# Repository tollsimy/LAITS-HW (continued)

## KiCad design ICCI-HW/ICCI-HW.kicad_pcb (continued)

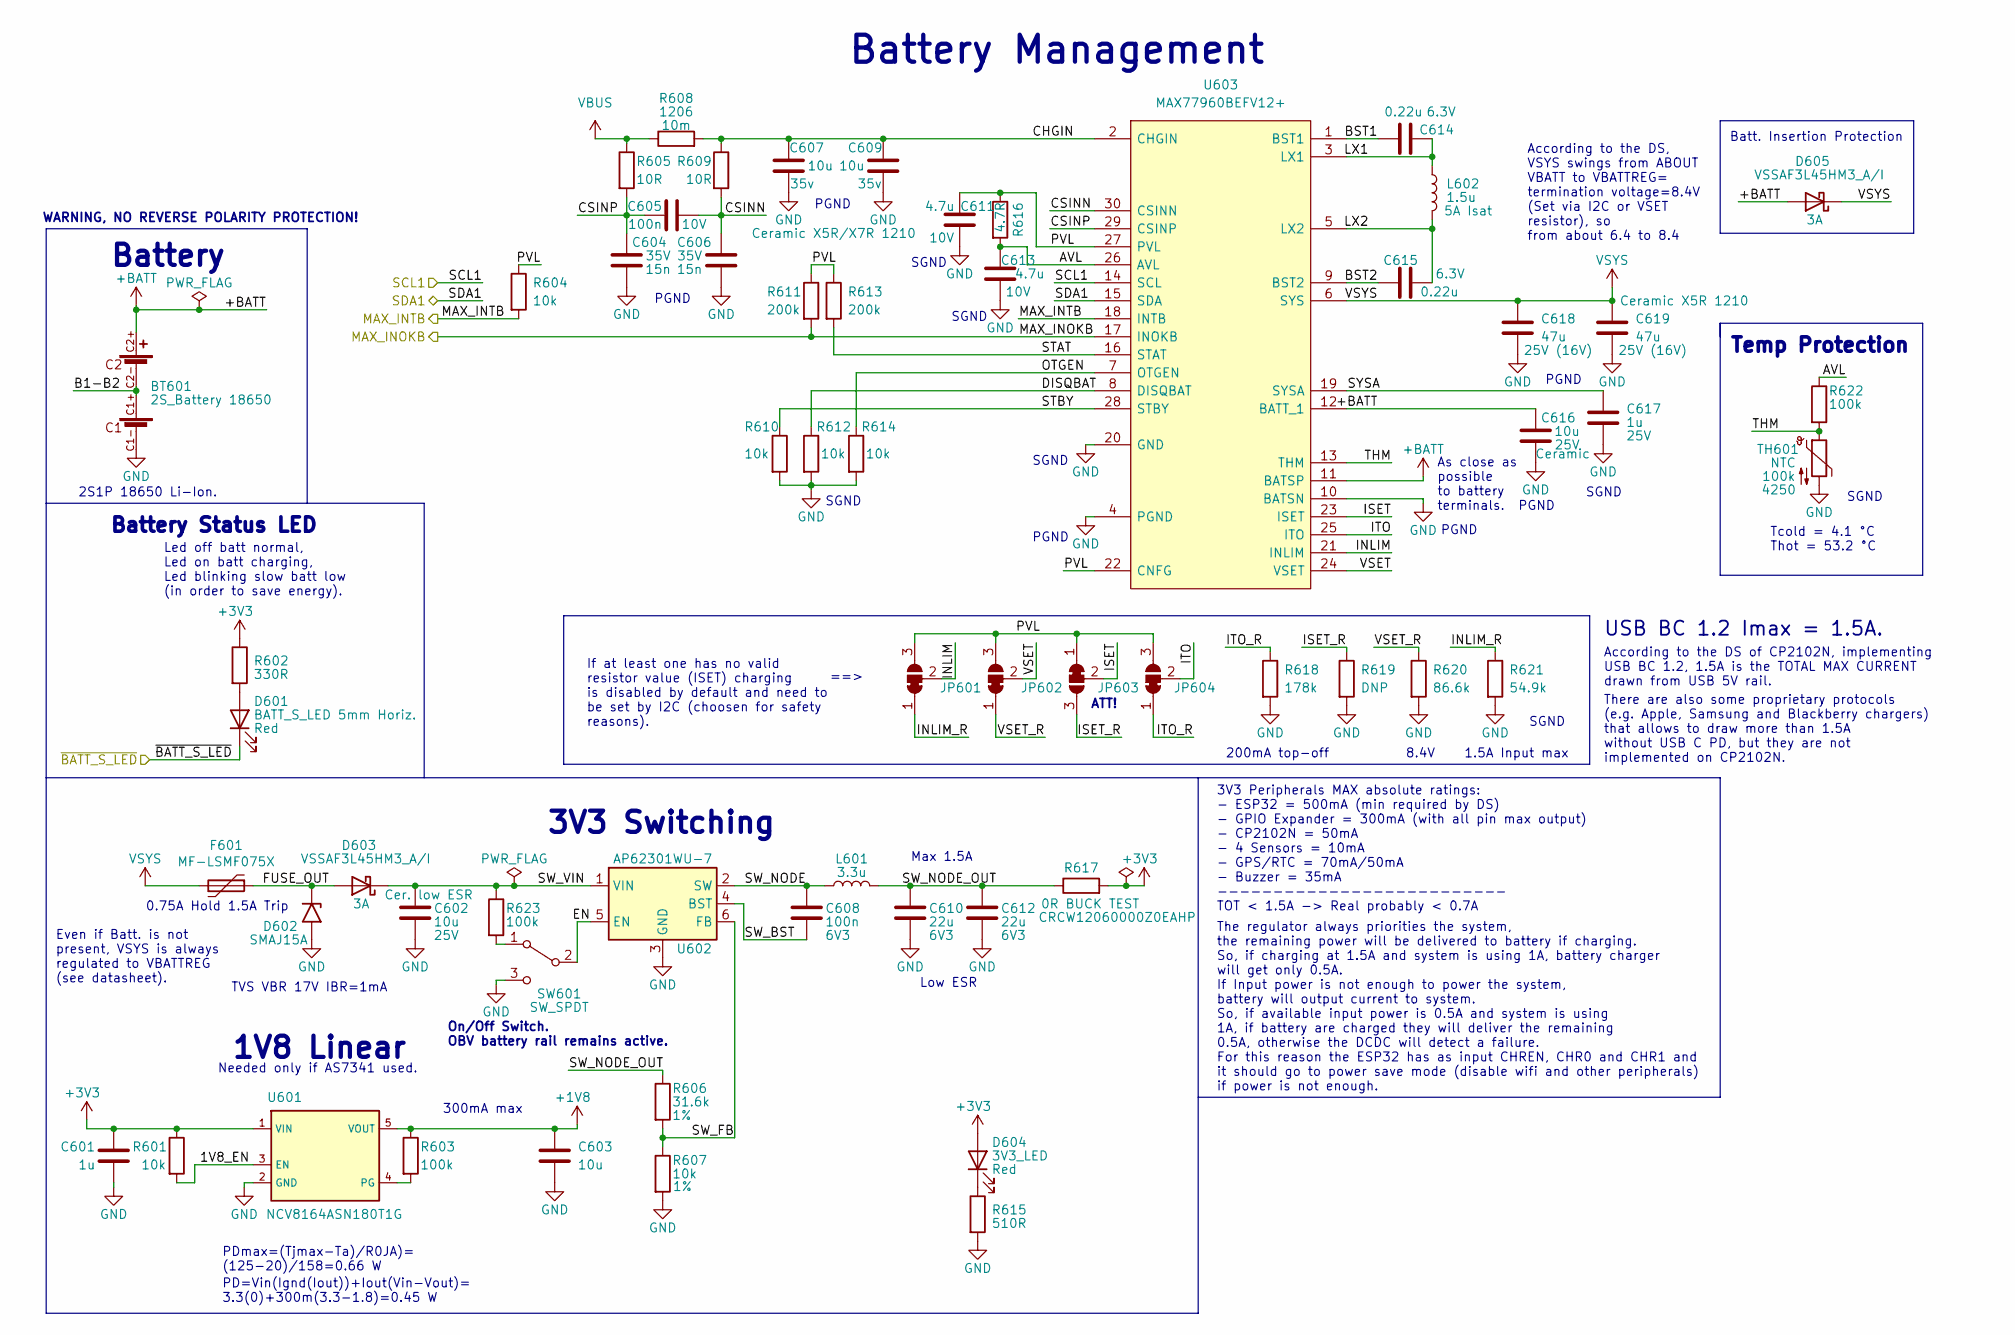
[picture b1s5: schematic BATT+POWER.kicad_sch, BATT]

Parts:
BT601: 2S_Battery 18650; BAT_1048
C601: 1u; C_0603_1608Metric
C602, C616: 10u; C_1206_3216Metric; Voltage 25V
C603: 10u; C_1206_3216Metric
C604, C606: 15n; C_0603_1608Metric; Voltage 35V
C605: 100n; C_0603_1608Metric; Voltage 10V
C607, C609: 10u; C_1206_3216Metric; Voltage 35v
C608: 100n; C_0603_1608Metric; Voltage 6V3
C610, C612: 22u; C_1206_3216Metric; Voltage 6V3
C611, C613: 4.7u; C_0603_1608Metric; Voltage 10V
C614, C615: 0.22u; C_0603_1608Metric; Voltage 6.3V
C617: 1u; C_0603_1608Metric; Voltage 25V
C618, C619: 47u; C_1210_3225Metric; Voltage 25V (16V)
D601: BATT_S_LED 5mm Horiz.; LED_D5.0mm_Horizontal_O3.81mm_Z3.0mm
D602: SMAJ15A
D603, D605: VSSAF3L45HM3_A/I; VSSAF3L45HM3
D604: 3V3_LED; LED_0805_2012Metric
F601: MF-LSMF075X; Bourns_MF-LSMF
JP601, JP602, JP603, JP604: SolderJumper_3_Bridged12; SolderJumper-3_P1.3mm_Open_RoundedPad1.0x1.5mm_NumberLabels
L601: 3.3u; ICCI_L_Bourns_SRP7028A_7.3x6.6mm
L602: 1.5u; ICCI_L_Coilcraft_XxL4040; Current Rating 5A Isat
R601, R604, R610, R612, R614: 10k; R_0603_1608Metric
R602: 330R; R_0603_1608Metric
R603, R622, R623: 100k; R_0603_1608Metric
R605, R609: 10R; R_0603_1608Metric
R606: 31.6k; R_0603_1608Metric; Tolerance 1%
R607: 10k; R_0603_1608Metric; Tolerance 1%
R608: 10m; R_1206_3216Metric
R611, R613: 200k; R_0603_1608Metric
R615: 510R; R_0603_1608Metric
R616: 4.7R; R_0603_1608Metric
R617: 0R BUCK TEST; R_1206_3216Metric
R618: 178k; R_0603_1608Metric
R619: DNP; R_0603_1608Metric
R620: 86.6k; R_0603_1608Metric
R621: 54.9k; R_0603_1608Metric
SW601: SW_SPDT; OS102011MA1QN1
TH601: NTC; R_0603_1608Metric
U601: NCV8164ASN180T1G
U602: AP62301WU-7; TSOT-23-6
U603: MAX77960BEFV12+; Manufacturer_Part_Number MAX77960EFV06+; Mouser Part Number 700-MAX77960EFV06+

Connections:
+1V8: C603.1, R603.1, U601.5 (VOUT); also elsewhere on the board
+3V3: C601.1, D604.2 (A), R601.1, R602.1, R617.2, U601.1 (VIN); also elsewhere on the board
+BATT: BT601.C2+, C616.1, D605.2 (A), U603.11 (BATSP), U603.12 (BATT_1); also elsewhere on the board
/AUX + Peripherals/SCL1: U603.14 (SCL); also elsewhere on the board
/AUX + Peripherals/SDA1: U603.15 (SDA); also elsewhere on the board
/BATT + POWER/1V8_EN: R601.2, U601.3 (EN)
/BATT + POWER/AVL: C613.1, R616.2, R622.1, U603.26 (AVL)
/BATT + POWER/B1-B2: BT601.C1+, BT601.C2-
/BATT + POWER/BST1: C614.1, U603.1 (BST1)
/BATT + POWER/BST2: C615.1, U603.9 (BST2)
/BATT + POWER/CHGIN: C607.1, C609.1, R608.2, R609.1, U603.2 (CHGIN)
/BATT + POWER/CSINN: C605.2, C606.2, R609.2, U603.30 (CSINN)
/BATT + POWER/CSINP: C604.2, C605.1, R605.2, U603.29 (CSINP)
/BATT + POWER/DISQBAT: R612.1, U603.8 (DISQBAT)
/BATT + POWER/EN: SW601.2 (B), U602.5 (EN)
/BATT + POWER/FUSE_OUT: D602.1 (A1), D603.2 (A), F601.1
/BATT + POWER/INLIM: JP601.2 (C), U603.21 (INLIM)
/BATT + POWER/INLIM_R: JP601.1 (A), R621.1
/BATT + POWER/ISET: JP603.2 (C), U603.23 (ISET)
/BATT + POWER/ISET_R: JP603.3 (B), R619.1
/BATT + POWER/ITO: JP604.2 (C), U603.25 (ITO)
/BATT + POWER/ITO_R: JP604.1 (A), R618.1
/BATT + POWER/LX1: C614.2, L602.1, U603.3 (LX1)
/BATT + POWER/LX2: C615.2, L602.2, U603.5 (LX2)
/BATT + POWER/MAX_INOKB: R611.2, U603.17 (INOKB); also elsewhere on the board
/BATT + POWER/MAX_INTB: R604.2, U603.18 (INTB); also elsewhere on the board
/BATT + POWER/OTGEN: R614.1, U603.7 (OTGEN)
/BATT + POWER/PVL: C611.1, JP601.3 (B), JP602.3 (B), JP603.1 (A), JP604.3 (B), R604.1, R611.1, R613.1, R616.1, U603.22 (CNFG), U603.27 (PVL)
/BATT + POWER/STAT: R613.2, U603.16 (STAT)
/BATT + POWER/STBY: R610.1, U603.28 (STBY)
/BATT + POWER/SW_BST: C608.2, U602.4 (BST)
/BATT + POWER/SW_FB: R606.2, R607.1, U602.6 (FB)
/BATT + POWER/SW_NODE: C608.1, L601.1, U602.2 (SW)
/BATT + POWER/SW_NODE_OUT: C610.1, C612.1, L601.2, R606.1, R617.1
/BATT + POWER/SW_VIN: C602.1, D603.1 (K), R623.1, U602.1 (VIN)
/BATT + POWER/SYSA: C617.1, U603.19 (SYSA)
/BATT + POWER/THM: R622.2, TH601.1, U603.13 (THM)
/BATT + POWER/VSET: JP602.2 (C), U603.24 (VSET)
/BATT + POWER/VSET_R: JP602.1 (A), R620.1
/BATT + POWER/~BATT_S_LED: D601.1 (K); also elsewhere on the board
GND: BT601.C1-, C601.2, C602.2, C603.2, C604.1, C606.1, C607.2, C609.2, C610.2, C611.2, C612.2, C613.2, C616.2, C617.2, C618.2, C619.2, D602.2 (A2), R607.2, R610.2, R612.2, R614.2, R615.2, R618.2, R619.2, R620.2, R621.2, SW601.3 (C), TH601.2, U601.2 (GND), U602.3 (GND), U603.4 (PGND), U603.10 (BATSN), U603.20 (GND); also elsewhere on the board
unnamed: D601.2 (A), R602.2
unnamed: D604.1 (K), R615.1
unnamed: R603.2, U601.4 (PG)
unnamed: R623.2, SW601.1 (A)
VBUS: R605.1, R608.1; also elsewhere on the board
VCC: C618.1, C619.1, D605.1 (K), F601.2, U603.6 (SYS); also elsewhere on the board

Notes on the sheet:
ATT!
SGND
Battery Management
3V3 Switching
Battery
TVS VBR 17V IBR=1mA
3V3 Peripherals MAX absolute ratings: - ESP32 = 500mA (min required by DS) - GPIO Expander = 300mA (with all pin max output) - CP2102N = 50mA - 4 Sensors = 10mA - GPS/RTC = 70mA/50mA - Buzzer = 35mA -------------------------- TOT < 1.5A -> Real probably < 0.7A
PGND
1.5A Input max
If at least one has no valid resistor value (ISET) charging is disabled by default and need to be set by I2C (choosen for safety reasons).
Batt. Insertion Protection
Needed only if AS7341 used.
PD=Vin(Ignd(Iout))+Iout(Vin-Vout)= 3.3(0)+300m(3.3-1.8)=0.45 W
Even if Batt. is not present, VSYS is always regulated to VBATTREG (see datasheet).
There are also some proprietary protocols (e.g. Apple, Samsung and Blackberry chargers) that allows to draw more than 1.5A without USB C PD, but they are not implemented on CP2102N.
Led off batt normal, Led on batt charging, Led blinking slow batt low (in order to save energy).
Temp Protection
300mA max
8.4V
Tcold = 4.1 °C Thot = 53.2 °C
PDmax=(Tjmax-Ta)/R0JA)= (125-20)/158=0.66 W
USB BC 1.2 Imax = 1.5A.
WARNING, NO REVERSE POLARITY PROTECTION!
Max 1.5A
200mA top-off
The regulator always priorities the system, the remaining power will be delivered to battery if charging. So, if charging at 1.5A and system is using 1A, battery charger will get only 0.5A. If Input power is not enough to power the system, battery will output current to system. So, if available inp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
On/Off Switch. OBV battery rail remains active.
0.75A Hold 1.5A Trip
Battery Status LED
==>
As close as possible to battery terminals.
2S1P 18650 Li-Ion.
Low ESR
According to the DS of CP2102N, implementing USB BC 1.2, 1.5A is the TOTAL MAX CURRENT drawn from USB 5V rail.
1V8 Linear
According to the DS, VSYS swings from ABOUT VBATT to VBATTREG= termination voltage=8.4V (Set via I2C or VSET resistor), so from about 6.4 to 8.4

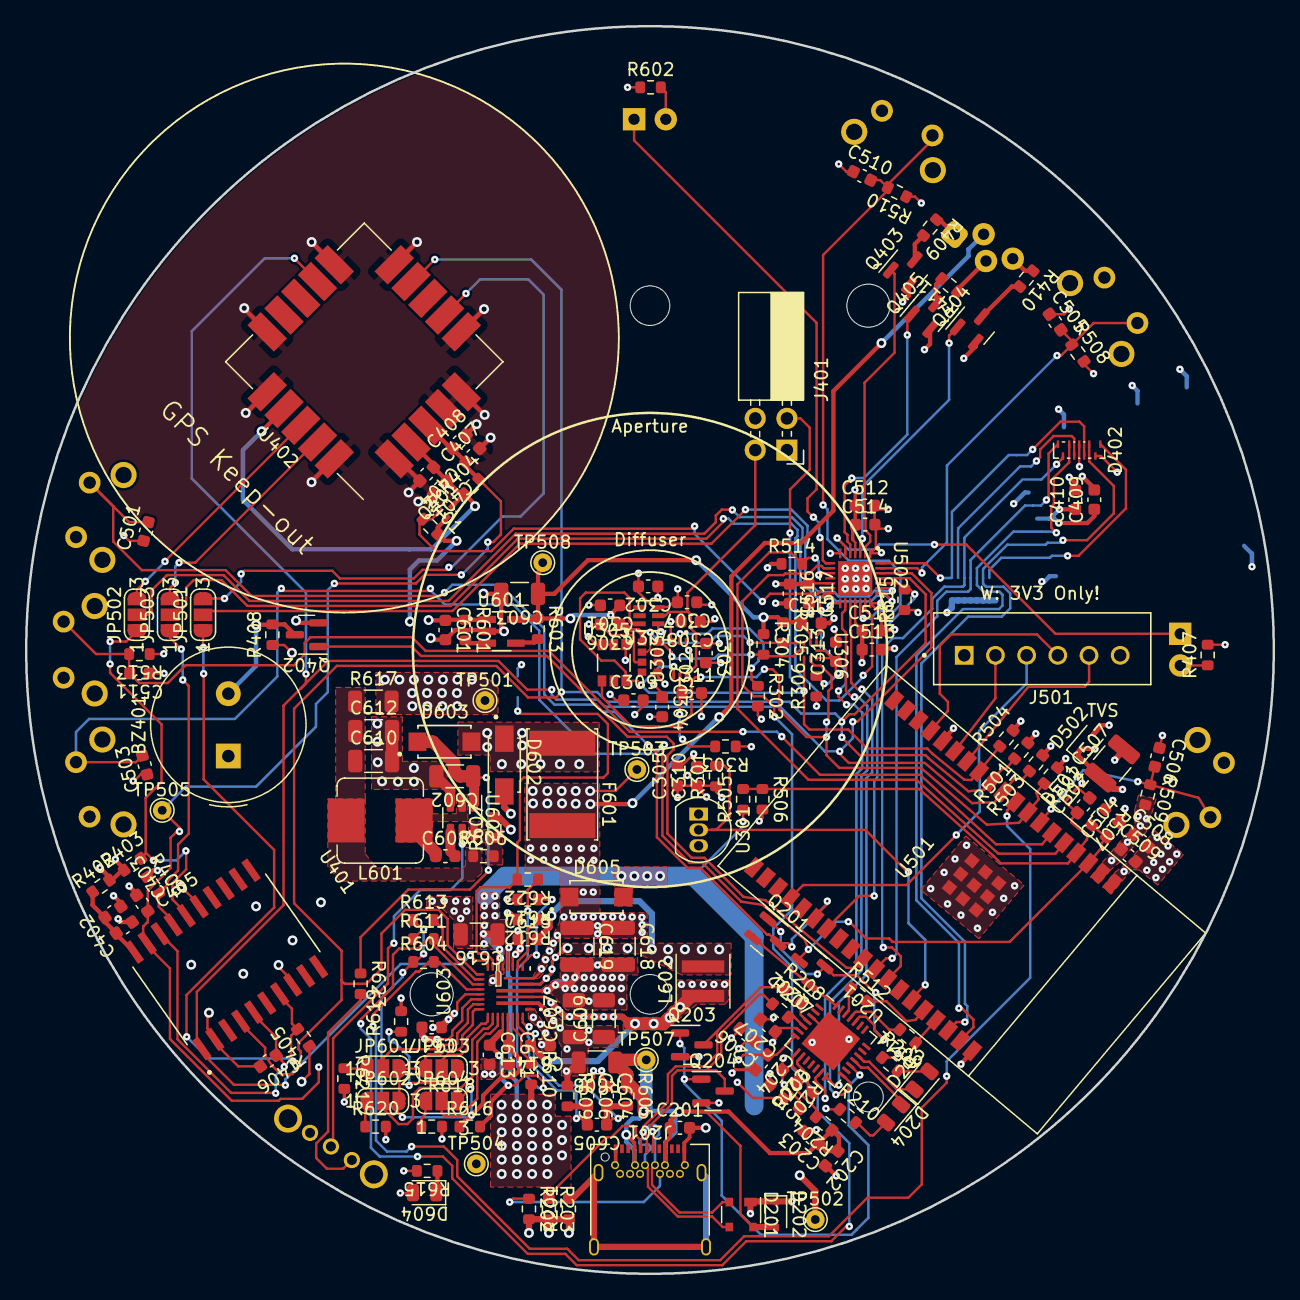
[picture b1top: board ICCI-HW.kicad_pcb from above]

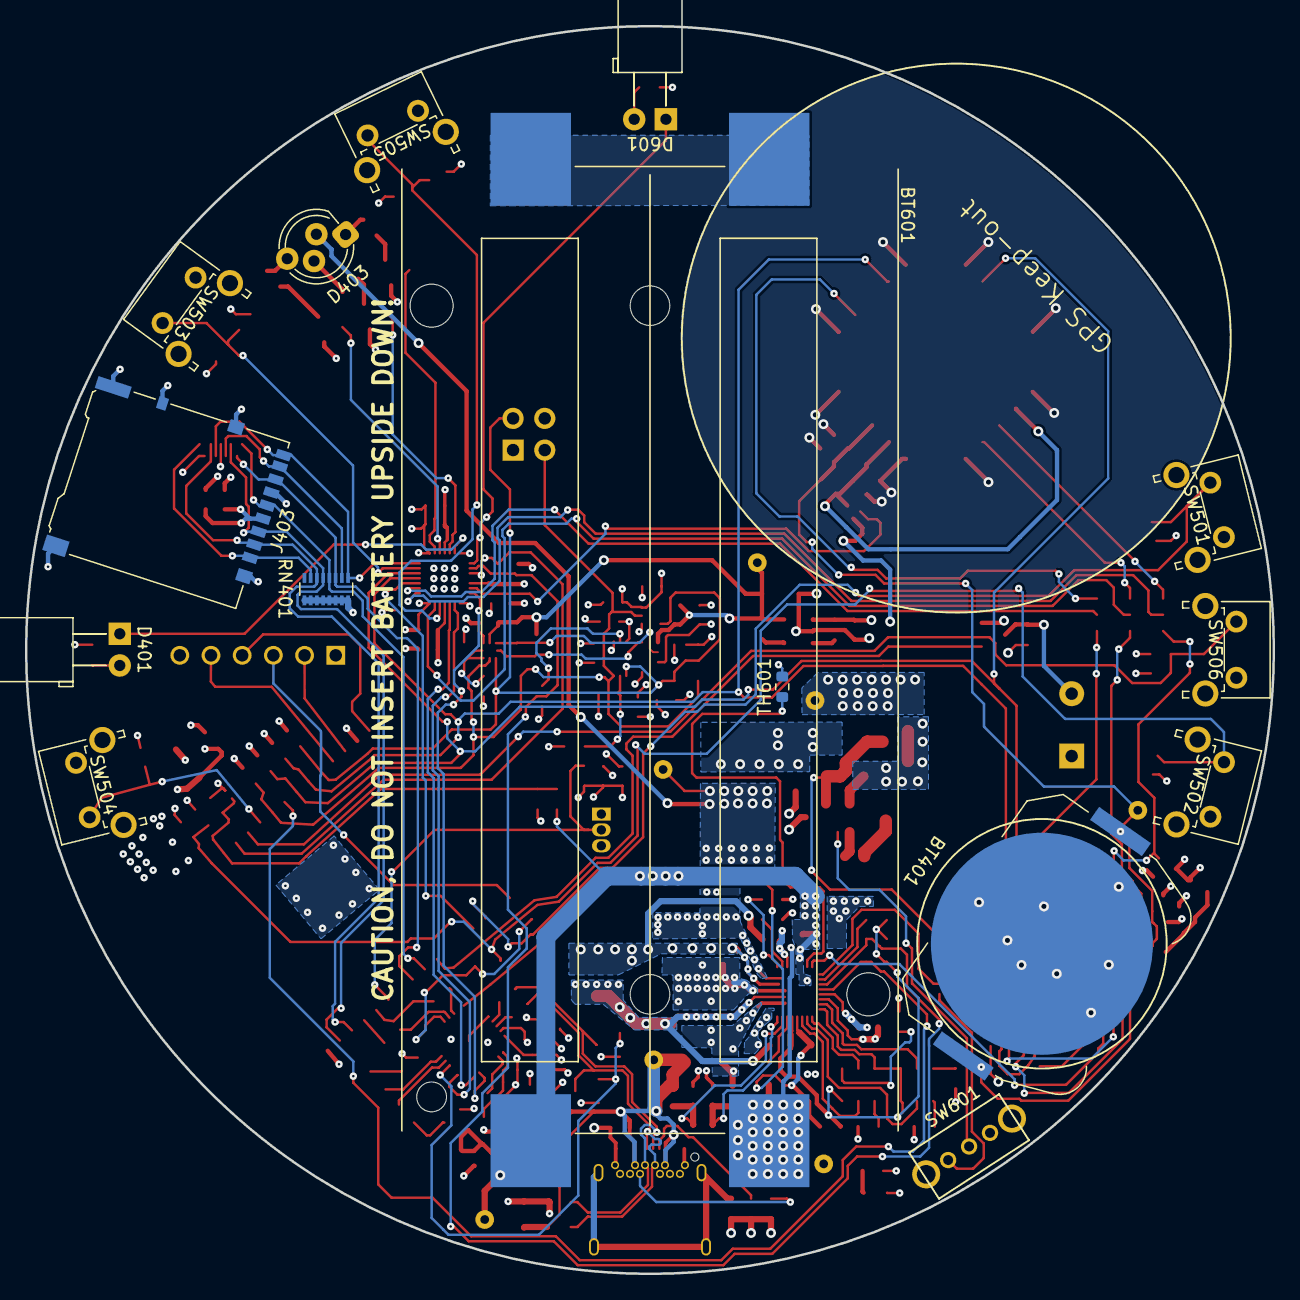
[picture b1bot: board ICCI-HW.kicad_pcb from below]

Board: 4 copper layers, 100.0 x 100.0 mm, 201 parts (15 on the bottom side), 125 nets.

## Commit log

2022-05-10 rtc + sensors
2022-05-11 usb PD started
2022-05-20 add GPIO Expansion
2022-05-23 schematic V1.0
2022-05-23 footprint assigned
2022-05-23 start layout
2022-05-23 change MAX77962 (BGA) to MAX77960B (FC2QFN)
2022-05-31 fw: updates
2022-07-15 hw: updates
2022-07-22 layout updates
2022-07-25 layout PCB V1.0
2022-07-26 hw: fix missing contact from SYS to SYSA on MAX77960
2022-07-26 change name from ICCI to LAITS
2022-07-27 improved silkscreen placement and some minor changes
2022-07-27 generate JLCPCB Gerber Outputs
2022-07-27 improved silkscreen and add JLCPCB Ordering Instructions
2022-07-28 fix USB trace clearance
2022-07-28 rename gerbers.zip
2022-08-01 add .step board file
2022-08-01 remove wrong inductor from BOM
2022-08-08 3D mody indep. path (alias)
2022-08-08 generate IBOM
2022-08-08 fix bug indep. path
2022-08-08 update gitignore
2022-08-08 add BOM files
2022-08-10 Patch 1.0.1
    Bug:
    - Changed U602 footprint from TSOT26 to SOT563 in order to reflect pin assignment.
    Small bugs:
    - Missing silkscreen for SMD leds info (3V3, RX, TX)
    - DS18B20 silkscreen now reflect horizontal placement
    - Rotated and modified the pinout of the jumper JP603 so now it's clear that it is connected different in respect to JP601, JP602, JP604
2022-08-10 Updated BOM to patch 1.0.1
2022-08-11 Fixed a minor bug in the assignment of SDA0 and SCL0 pins, doesn't affect Hardware, swap in firmware
2022-08-25 Now LAITS notify charge state also when turned off
2022-08-26 removed useless file
2022-08-27 Marked C501 as DNP to ensure proper startup sequence
2022-09-02 Add small info about ESP antenna selector on schematic
